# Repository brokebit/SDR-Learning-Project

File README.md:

# SDR-Learning-Project
Repository of stuff to learn about and build an SDR
# Learning Projects
- [Mixer Board](https://github.com/brokebit/SDR-Learning-Project/tree/main/Mixer%20Board/TS3A5017-Mixer) TS3A5017 (Direct Reciever)
- Op Amp
- Front End Amp
- Frequency Synthesizer
- Bandpass Filter 
  
# SDR Radio Research

## Chips
- Mixer: TS3A5017
- Mixer: FST3253
- VFO: Si5351A
- DSP: F-V1
- DSP/Micro: https://docs.ai-thinker.com/en/esp32-a1s
- OpAmp: LMP7715
- OpAmp: LM4562
- OpAmp: THS4304 / LT1818
    - https://www.ti.com/lit/gpn/ths4304
    - 
  
## Basics
### Quadrature Signals
- https://www.ieee.li/pdf/essay/quadrature_signals.pdf
### Phase Locked Loop (PLL): 
Create stable signal reference. Use a stable low freq reference (Crystal) to stabilize a high freq unstable ref (VCO). 
- https://www.youtube.com/watch?v=A9qt0JYdvFU
- https://www.youtube.com/watch?v=P8agoshy3H4
- https://www.youtube.com/watch?v=CM8n3wzNOvc
### Voltage Controlled Oscillator (VCO)
- Usually unstable, and require something like a PLL to stabilize 
### Operational Amplifiers
- https://www.youtube.com/watch?v=7FYHt5XviKc
- Gain is huge
- In open loop configuration, they are just comparators; Add negative feedback to become amplifiers rather than comparators
- If non-inverting input is higher than inverting input, output will be V+
- If non-inverting input is lower than inverting input, output will be V-
- Called "Operational" cause they were designed to perform mathematical "operations."
- Can be used as a buffer in buffer configuration
- Input impedance is high, so won’t draw current or effect anything on the input side
- Output impedance is low, so you can drive a bit of current through it. Tens of milliamps
- Non-Inverting Amp Configuration (Single Ended Amp)
    - Gain = Rf/R1 + 1
- Inverting Amp configuration
    - Gain = Rf/R1
    - Input * Gain * -1
    - With DC supply, it can never go negative. So need to off set and can do that by supply 1/2 Vcc to non-inverting pin

## Radio Designs
- https://circuitsalad.com/wp-content/uploads/2020/05/si5351_sdr3.jpg
- NA5Y - https://www.youtube.com/watch?v=prCrbD4T6I4
- NA5Y - https://www.youtube.com/watch?v=redvZ7LcXT0&t=171s
- https://www.zachtek.com/

## Filters
### Receive 
- https://qrp-labs.com/images/bpfkit/bpf3.pdf
- 
### Transmit
- 

## Mixing and Switching
- VFO (SI5351A): https://www.youtube.com/watch?v=9Dz9BO6VJIk
- Mixers Part I: https://www.youtube.com/watch?v=uiTrCUNRUIA
- Mixers Part II: https://www.youtube.com/watch?v=nGOxNGZQ0EM
- Mixer: https://www.youtube.com/watch?v=JuuKF1RFvBM
- 
https://www.allaboutcircuits.com/technical-articles/how-to-multiply-RF-signals-without-a-multiplier-the-switching-mixer/

### Tayloe Detector/Mixer:
- https://norcalqrp.org/files/Tayloe_mixer_x3a.pdf
- https://www.youtube.com/watch?v=EarY64Lf3ls&t=327s
- https://github.com/thaaraak/Tayloe-Mixer-v3

## RF Board Design
### Research needed
- Impedance and traces - Use either JLC PCB impedance calculator or one built into KiCad
- Stackups and Ground planes - Use four layers or more. Put RF traces on top or bottom layers. Always a Ground plane above or bellow the RF layer for return currents
- Stripline: Internal Trace
- Microstrip: Outer layer trace

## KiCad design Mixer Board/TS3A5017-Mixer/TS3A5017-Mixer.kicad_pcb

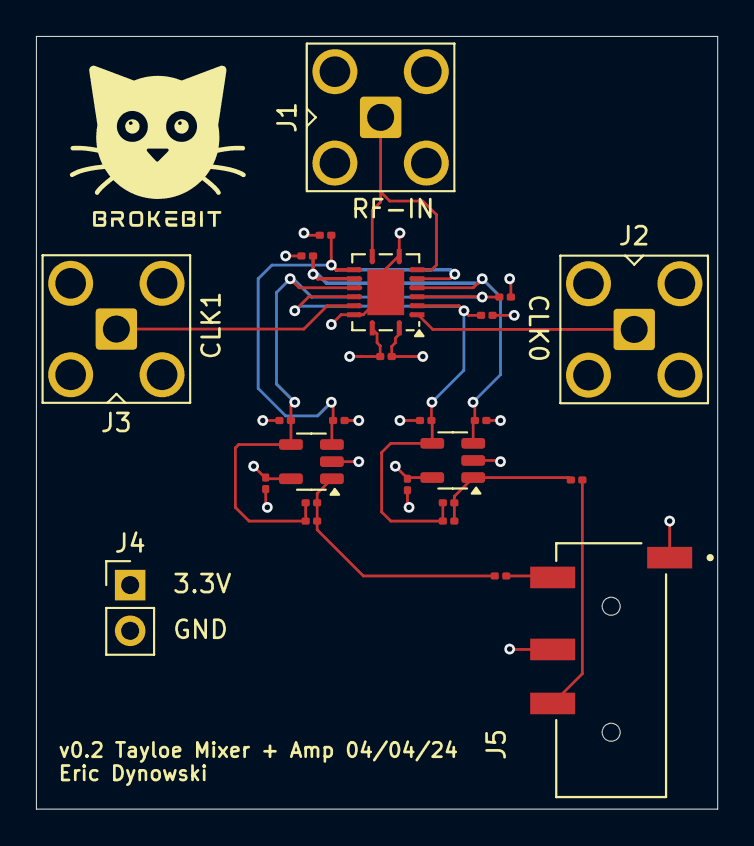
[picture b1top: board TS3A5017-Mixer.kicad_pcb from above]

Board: 4 copper layers, 37.8 x 42.9 mm, 25 parts (0 on the bottom side), 13 nets.

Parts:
C1, C2, C3, C4, C5, C6, C7, C8, C9, C10, C11, C12, C13: .1uf; C_0201_0603Metric
C14, C15: 1uf; C_0201_0603Metric
J1: RF-In; SMA_Amphenol_901-143_Horizontal
J2: CLK0; SMA_Amphenol_901-143_Horizontal
J3: CLK1; SMA_Amphenol_901-143_Horizontal
J4: Conn_01x02_Pin; PinHeader_1x02_P2.54mm_Vertical
J5: PJ-320D-A; HRO_PJ-320D-A
R1, R2: 10k; R_0201_0603Metric
U1: TS3A5017RGY; Texas_RGY_R-PVQFN-N16_EP2.05x2.55mm
U2, U3: LMP7715MF; SOT-23-5

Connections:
/3.3V: C1.1, C6.2, C10.2, J4.1, U1.16 (V+), U2.5 (V+), U3.5 (V+)
/I-Neg: C2.1, C12.2, C13.2, R2.1, U1.3 (1S4), U1.13 (2S4), U3.4 (IN-)
/I-Pos: C4.1, C11.2, U1.5 (1S2), U1.11 (2S2), U3.3 (IN+)
/Q-Neg: C3.1, C7.2, C8.2, R1.1, U1.4 (1S3), U1.12 (2S3), U2.4 (IN-)
/Q-Pos: C5.1, C9.2, U1.6 (1S1), U1.10 (2S1), U2.3 (IN+)
CLK0: J2.1 (In), U1.2 (IN2)
CLK1: J3.1 (In), U1.14 (IN1)
GND: C1.2, C2.2, C3.2, C4.2, C5.2, C6.1, C8.1, C9.1, C10.1, C11.1, C12.1, J1.2 (Ext), J2.2 (Ext), J3.2 (Ext), J4.2, J5.1, J5.3, U1.1 (1~EN), U1.8 (GND), U1.15 (2~EN), U1.17 (GND), U2.2 (V-), U3.2 (V-)
unnamed: C14.1, J5.4
unnamed: C15.2, J5.2
unnamed: C7.1, C15.1, R1.2, U2.1 (OUT)
unnamed: C13.1, C14.2, R2.2, U3.1 (OUT)
RF-In: J1.1 (In), U1.7 (1D), U1.9 (2D)

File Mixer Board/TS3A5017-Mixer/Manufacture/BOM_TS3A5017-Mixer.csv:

"Id";"Designator";"Footprint";"Quantity";"Designation";"Supplier and ref";
1;"C4,C5,C10,C9,C3,C12,C6,C8,C13,C11,C2,C7";"C_0201_0603Metric";12;".1uf";;;
2;"C1";"C_0603_1608Metric";1;".1uf";;;
3;"U1";"Texas_RGY_R-PVQFN-N16_EP2.05x2.55mm";1;"TS3A5017RGY";;;
4;"J3";"SMA_Amphenol_901-143_Horizontal";1;"CLK1";;;
5;"J4";"PinHeader_1x02_P2.54mm_Vertical";1;"Conn_01x02_Pin";;;
6;"C14,C15";"C_0201_0603Metric";2;"1uf";;;
7;"J1";"SMA_Amphenol_901-143_Horizontal";1;"RF-In";;;
8;"J2";"SMA_Amphenol_901-143_Horizontal";1;"CLK0";;;
9;"R1,R2";"R_0201_0603Metric";2;"10k";;;
10;"U2,U3";"SOT-23-5";2;"LMP7715MF";;;
11;"J5";"HRO_PJ-320D-A";1;"PJ-320D-A";;;

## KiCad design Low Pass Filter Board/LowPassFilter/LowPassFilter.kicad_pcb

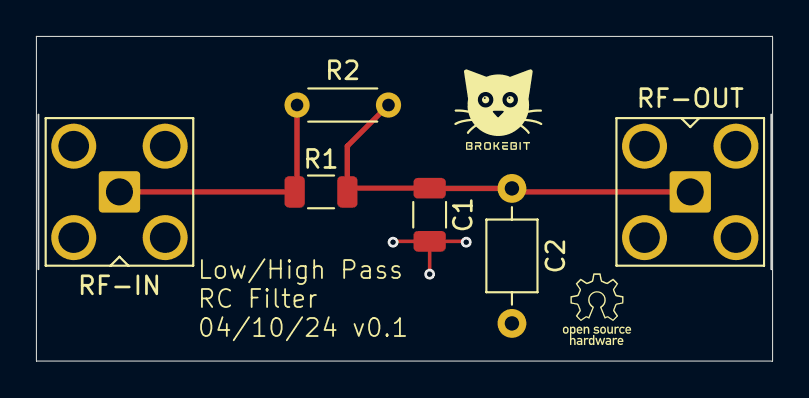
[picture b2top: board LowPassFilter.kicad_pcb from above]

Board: 4 copper layers, 40.9 x 18.0 mm, 6 parts (0 on the bottom side), 3 nets.

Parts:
C1: C; C_1206_3216Metric
C2: C; C_Axial_L3.8mm_D2.6mm_P7.50mm_Horizontal
R1: R_Small_US; R_1206_3216Metric
R2: R_Small_US; R_Axial_DIN0204_L3.6mm_D1.6mm_P5.08mm_Horizontal
RF-IN: Conn_Coaxial_Small; SMA_Amphenol_901-143_Horizontal
RF-OUT: Conn_Coaxial_Small; SMA_Amphenol_901-143_Horizontal

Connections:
GND: C1.2, C2.2, RF-IN.2 (Ext), RF-OUT.2 (Ext)
unnamed: R1.1, R2.1, RF-IN.1 (In)
unnamed: C1.1, C2.1, R1.2, R2.2, RF-OUT.1 (In)

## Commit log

2024-03-23 Fix Spelling
2024-03-23 Updates on OpAmps
2024-03-23 PLL UPdate
2024-03-25 Add start of mixerboard
2024-03-25 Working on board
2024-03-25 Continued work and first iteration
2024-03-25 Finish first iteration, generate manufacturing files
2024-04-02 Working on stuff
2024-04-02 Compare README
2024-04-02 Working on mixer board
2024-04-04 Workig on mixer board
2024-04-05 Remove .DS_Store from everywhere
2024-04-05 Add .gitignore
2024-04-10 Working on silkscreen and ordering
2024-04-10 Add drill files
2024-04-13 Fixing things
